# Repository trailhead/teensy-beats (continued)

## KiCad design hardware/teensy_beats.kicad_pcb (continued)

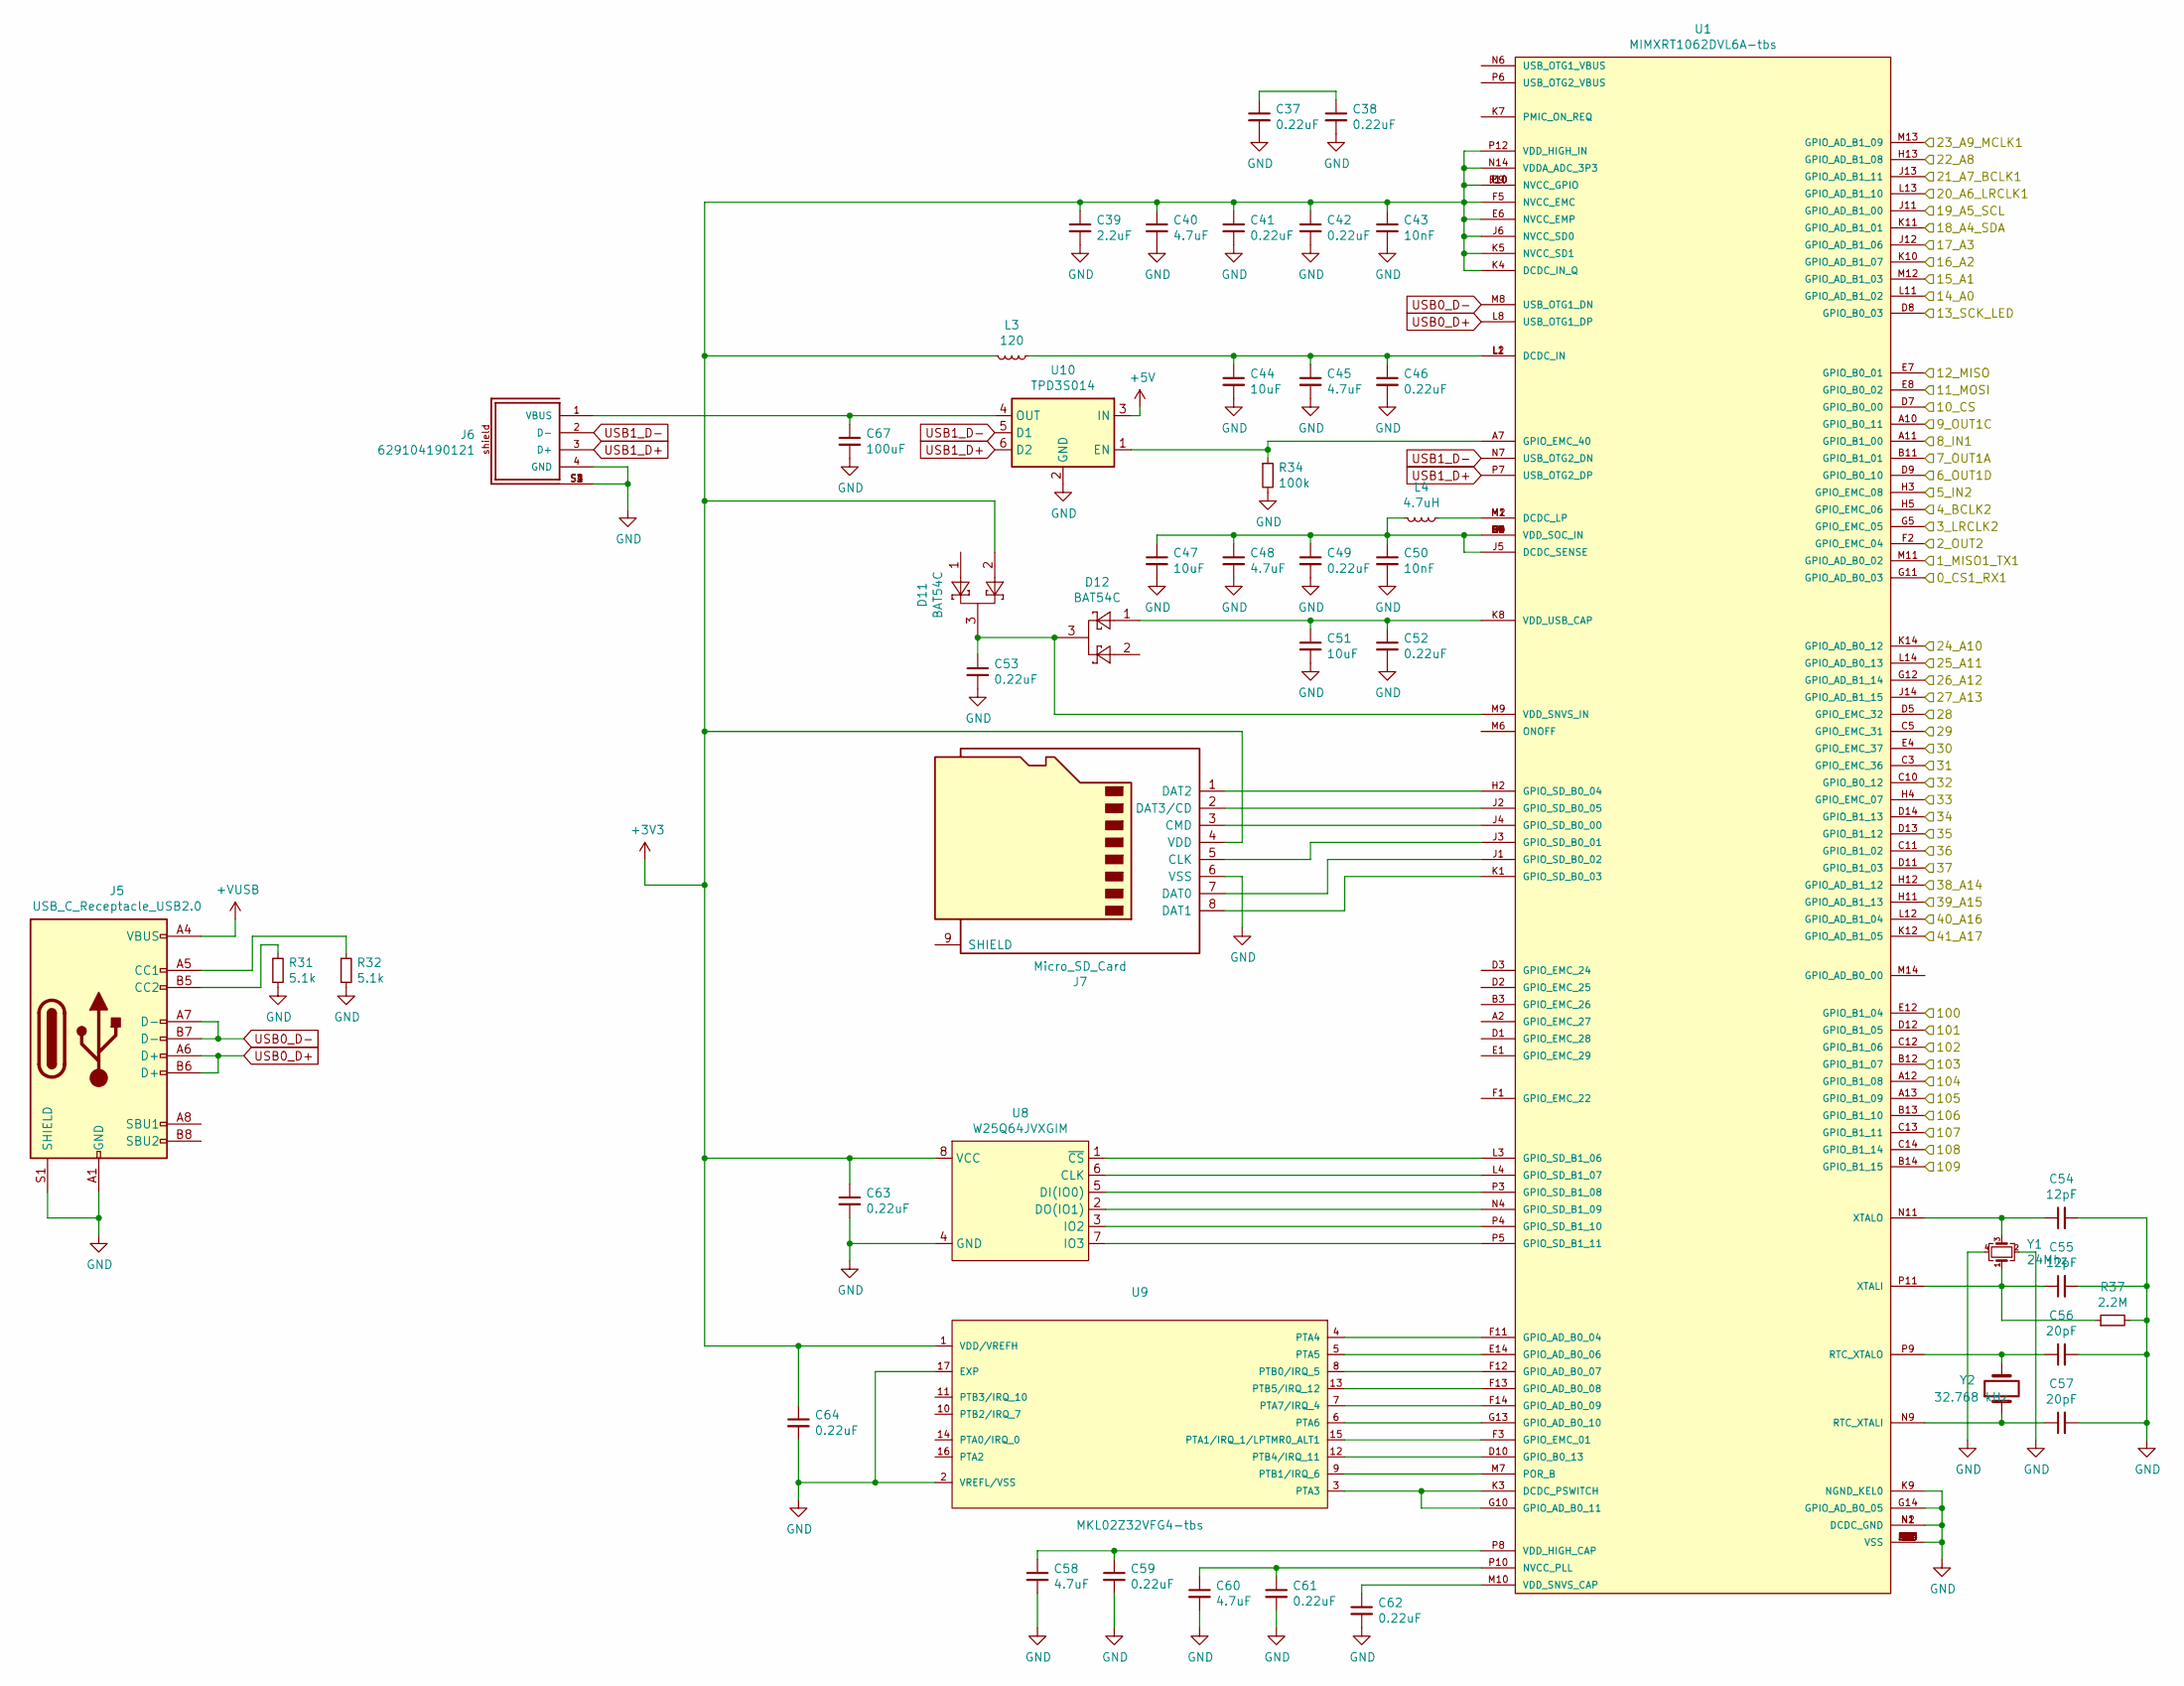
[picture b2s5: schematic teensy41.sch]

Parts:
C37, C38, C41, C42, C46, C49, C52, C53, C59, C61, C62, C63, C64: 0.22uF; C_0402_1005Metric
C39: 2.2uF; C_0805_2012Metric
C40, C45, C48, C58, C60: 4.7uF; C_0603_1608Metric
C43: 10nF; C_0402_1005Metric
C44, C47, C51: 10uF; C_0603_1608Metric
C50: 10nF; C_0603_1608Metric
C54, C55: 12pF; C_0402_1005Metric
C56, C57: 20pF; C_0402_1005Metric
C67: 100uF; C_0603_1608Metric
D11, D12: BAT54C; SOT-23
J5: USB_C_Receptacle_USB2.0; MOLEX_105450-0101
J6: 629104190121; PART-NUMBER 629104190121
J7: Micro_SD_Card; microSD_HC_Wuerth_693072010801
L3: 120; L_0603_1608Metric
L4: 4.7uH; L_1210_3225Metric
R31, R32: 5.1k; R_0402_1005Metric
R34: 100k; R_0402_1005Metric
R37: 2.2M; R_0402_1005Metric
U1: MIMXRT1062DVL6A-tbs; BGA196C80P14X14_1200X1200X161N; PARTREV 1.2
U8: W25Q64JVXGIM; SOIC-8_3.9x4.9mm_P1.27mm
U9: MKL02Z32VFG4-tbs; QFN50P300X300X65-17N
U10: TPD3S014; SOT-23-6
Y1: 24Mhz; Oscillator_SMD_Abracon_ASE-4Pin_3.2x2.5mm
Y2: 32.768 kHz; Crystal_SMD_MicroCrystal_CC7V-T1A-2Pin_3.2x1.5mm

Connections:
+3V3: C39.1, C40.1, C41.1, C42.1, C43.1, C63.1, C64.1, D11.2, J7.4 (VDD), L3.2, U1.E6 (NVCC_EMP), U1.E9 (NVCC_GPIO), U1.F5 (NVCC_EMC), U1.F10 (NVCC_GPIO), U1.J6 (NVCC_SD0), U1.J10 (NVCC_GPIO), U1.K4 (DCDC_IN_Q), U1.K5 (NVCC_SD1), U1.N14 (VDDA_ADC_3P3), U1.P12 (VDD_HIGH_IN), U8.8 (VCC), U9.1 (VDD/VREFH); also elsewhere on the board
+5V: U10.3 (IN); also elsewhere on the board
+VUSB: J5.A4 (VBUS), J5.A9 (VBUS), J5.B4 (VBUS), J5.B9 (VBUS); also elsewhere on the board
/Teensy4.1/15_A1: U1.M12 (GPIO_AD_B1_03)
/Teensy4.1/16_A2: U1.K10 (GPIO_AD_B1_07)
/Teensy4.1/17_A3: U1.J12 (GPIO_AD_B1_06)
/Teensy4.1/26_A12: U1.G12 (GPIO_AD_B1_14)
/Teensy4.1/27_A13: U1.J14 (GPIO_AD_B1_15)
/Teensy4.1/33: U1.H4 (GPIO_EMC_07)
/Teensy4.1/37: U1.D11 (GPIO_B1_03)
/Teensy4.1/40_A16: U1.L12 (GPIO_AD_B1_04)
/Teensy4.1/41_A17: U1.K12 (GPIO_AD_B1_05)
BATT_LEVEL: U1.H12 (GPIO_AD_B1_12); also elsewhere on the board
BATT_STAT1: U1.A10 (GPIO_B0_11); also elsewhere on the board
BATT_STAT2: U1.A11 (GPIO_B1_00); also elsewhere on the board
BCLK: U1.J13 (GPIO_AD_B1_11); also elsewhere on the board
BCLK2: U1.H5 (GPIO_EMC_06); also elsewhere on the board
CS: U1.D7 (GPIO_B0_00); also elsewhere on the board
DOUT2: U1.F2 (GPIO_EMC_04); also elsewhere on the board
E1A: U1.D14 (GPIO_B1_13); also elsewhere on the board
E1B: U1.D13 (GPIO_B1_12); also elsewhere on the board
E2A: U1.C10 (GPIO_B0_12); also elsewhere on the board
E2B: U1.C11 (GPIO_B1_02); also elsewhere on the board
E3A: U1.D5 (GPIO_EMC_32); also elsewhere on the board
E3B: U1.C5 (GPIO_EMC_31); also elsewhere on the board
E4A: U1.E4 (GPIO_EMC_37); also elsewhere on the board
E4B: U1.C3 (GPIO_EMC_36); also elsewhere on the board
GND: C37.2, C38.2, C39.2, C40.2, C41.2, C42.2, C43.2, C44.2, C45.2, C46.2, C47.2, C48.2, C49.2, C50.2, C51.2, C52.2, C53.2, C54.2, C55.2, C56.2, C57.2, C58.2, C59.2, C60.2, C61.2, C62.2, C63.2, C64.2, C67.2, J5.A1 (GND), J5.A12 (GND), J5.B1 (GND), J5.B12 (GND), J5.S1 (SHIELD), J6.4 (GND), J6.S1, J6.S2, J6.S3, J6.S4, J7.6 (VSS), R31.2, R32.2, R34.2, R37.2, U1.A1 (VSS), U1.A14 (VSS), U1.B5 (VSS), U1.B10 (VSS), U1.E2 (VSS), U1.E13 (VSS), U1.G7 (VSS), U1.G8 (VSS), U1.G14 (GPIO_AD_B0_05), U1.H7 (VSS), U1.H8 (VSS), U1.J7 (VSS), U1.J8 (VSS), U1.K2 (VSS), U1.K9 (NGND_KEL0), U1.K13 (VSS), U1.L9 (VSS), U1.N1 (DCDC_GND), U1.N2 (DCDC_GND), U1.N5 (VSS), U1.N8 (VSS), U1.P1 (VSS), U1.P14 (VSS), U8.4 (GND), U9.2 (VREFL/VSS), U9.17 (EXP), U10.2 (GND), Y1.2, Y1.4; also elsewhere on the board
GPANAIO: U1.N10 (GPANAIO)
KEYPAD_C0: U1.B13 (GPIO_B1_10); also elsewhere on the board
KEYPAD_C1: U1.C12 (GPIO_B1_06); also elsewhere on the board
KEYPAD_C2: U1.A13 (GPIO_B1_09); also elsewhere on the board
KEYPAD_C3: U1.B12 (GPIO_B1_07); also elsewhere on the board
KEYPAD_C4: U1.A12 (GPIO_B1_08); also elsewhere on the board
KEYPAD_R0: U1.C13 (GPIO_B1_11); also elsewhere on the board
KEYPAD_R1: U1.C14 (GPIO_B1_14); also elsewhere on the board
KEYPAD_R2: U1.D12 (GPIO_B1_05); also elsewhere on the board
KEYPAD_R3: U1.E12 (GPIO_B1_04); also elsewhere on the board
KEYPAD_R4: U1.B14 (GPIO_B1_15); also elsewhere on the board
LRCLK: U1.L13 (GPIO_AD_B1_10); also elsewhere on the board
LRCLK2: U1.G5 (GPIO_EMC_05); also elsewhere on the board
MCLK: U1.M13 (GPIO_AD_B1_09); also elsewhere on the board
MISO: U1.E7 (GPIO_B0_01); also elsewhere on the board
MOSI: U1.E8 (GPIO_B0_02); also elsewhere on the board
unnamed: C37.1, C38.1
unnamed: C44.1, C45.1, C46.1, L3.1, U1.L1 (DCDC_IN), U1.L2 (DCDC_IN)
unnamed: C47.1, C48.1, C49.1, C50.1, L4.2, U1.F6 (VDD_SOC_IN), U1.F7 (VDD_SOC_IN), U1.F8 (VDD_SOC_IN), U1.F9 (VDD_SOC_IN), U1.G6 (VDD_SOC_IN), U1.G9 (VDD_SOC_IN), U1.H6 (VDD_SOC_IN), U1.H9 (VDD_SOC_IN), U1.J5 (DCDC_SENSE), U1.J9 (VDD_SOC_IN)
unnamed: C51.1, C52.1, D12.1, U1.K8 (VDD_USB_CAP)
unnamed: C53.1, D11.3, D12.3, U1.M9 (VDD_SNVS_IN)
unnamed: C54.1, U1.N11 (XTALO), Y1.3
unnamed: C55.1, R37.1, U1.P11 (XTALI), Y1.1
unnamed: C56.1, U1.P9 (RTC_XTALO), Y2.2
unnamed: C57.1, U1.N9 (RTC_XTALI), Y2.1
unnamed: C58.1, C59.1, U1.P8 (VDD_HIGH_CAP)
unnamed: C60.1, C61.1, U1.P10 (NVCC_PLL)
unnamed: C62.1, U1.M10 (VDD_SNVS_CAP)
unnamed: C67.1, J6.1 (VBUS), U10.4 (OUT)
unnamed: J5.A5 (CC1), R32.1
unnamed: J5.B5 (CC2), R31.1
unnamed: J7.1 (DAT2), U1.H2 (GPIO_SD_B0_04)
unnamed: J7.2 (DAT3/CD), U1.J2 (GPIO_SD_B0_05)
unnamed: J7.3 (CMD), U1.J4 (GPIO_SD_B0_00)
unnamed: J7.5 (CLK), U1.J3 (GPIO_SD_B0_01)
unnamed: J7.7 (DAT0), U1.J1 (GPIO_SD_B0_02)
unnamed: J7.8 (DAT1), U1.K1 (GPIO_SD_B0_03)
unnamed: L4.1, U1.M1 (DCDC_LP), U1.M2 (DCDC_LP)
unnamed: R34.1, U1.A7 (GPIO_EMC_40), U10.1 (EN)
unnamed: U1.D10 (GPIO_B0_13), U9.12 (PTB4/IRQ_11)
unnamed: U1.E14 (GPIO_AD_B0_06), U9.5 (PTA5)
unnamed: U1.F3 (GPIO_EMC_01), U9.15 (PTA1/IRQ_1/LPTMR0_ALT1)
unnamed: U1.F11 (GPIO_AD_B0_04), U9.4 (PTA4)
unnamed: U1.F12 (GPIO_AD_B0_07), U9.8 (PTB0/IRQ_5)
unnamed: U1.F13 (GPIO_AD_B0_08), U9.13 (PTB5/IRQ_12)
unnamed: U1.F14 (GPIO_AD_B0_09), U9.7 (PTA7/IRQ_4)
unnamed: U1.G10 (GPIO_AD_B0_11), U1.K3 (DCDC_PSWITCH), U9.3 (PTA3)
unnamed: U1.G13 (GPIO_AD_B0_10), U9.6 (PTA6)
unnamed: U1.L3 (GPIO_SD_B1_06), U8.1 (~CS)
unnamed: U1.L4 (GPIO_SD_B1_07), U8.6 (CLK)
unnamed: U1.M7 (POR_B), U9.9 (PTB1/IRQ_6)
unnamed: U1.N4 (GPIO_SD_B1_09), U8.2 (DO(IO1))
unnamed: U1.P3 (GPIO_SD_B1_08), U8.5 (DI(IO0))
unnamed: U1.P4 (GPIO_SD_B1_10), U8.3 (IO2)
unnamed: U1.P5 (GPIO_SD_B1_11), U8.7 (IO3)
PCTL: U1.B11 (GPIO_B1_01); also elsewhere on the board
PHONE_DET: U1.H11 (GPIO_AD_B1_13); also elsewhere on the board
PWR_BTN: U1.K14 (GPIO_AD_B0_12); also elsewhere on the board
REC_LED: U1.H3 (GPIO_EMC_08); also elsewhere on the board
RGB_CLOCK: U1.M11 (GPIO_AD_B0_02); also elsewhere on the board
RGB_DATA: U1.G11 (GPIO_AD_B0_03); also elsewhere on the board
SCL: U1.J11 (GPIO_AD_B1_00); also elsewhere on the board
SCLK: U1.D8 (GPIO_B0_03); also elsewhere on the board
SDA: U1.K11 (GPIO_AD_B1_01); also elsewhere on the board
TFT_CS: U1.D9 (GPIO_B0_10); also elsewhere on the board
TFT_DC: U1.H13 (GPIO_AD_B1_08); also elsewhere on the board
TOUCH_CS: U1.L11 (GPIO_AD_B1_02); also elsewhere on the board
USB0_D+: J5.A6 (D+), J5.B6 (D+), U1.L8 (USB_OTG1_DP)
USB0_D-: J5.A7 (D-), J5.B7 (D-), U1.M8 (USB_OTG1_DN)
USB1_D+: J6.3 (D+), U1.P7 (USB_OTG2_DP), U10.6 (D2)
USB1_D-: J6.2 (D-), U1.N7 (USB_OTG2_DN), U10.5 (D1)
VOLUME: U1.L14 (GPIO_AD_B0_13); also elsewhere on the board

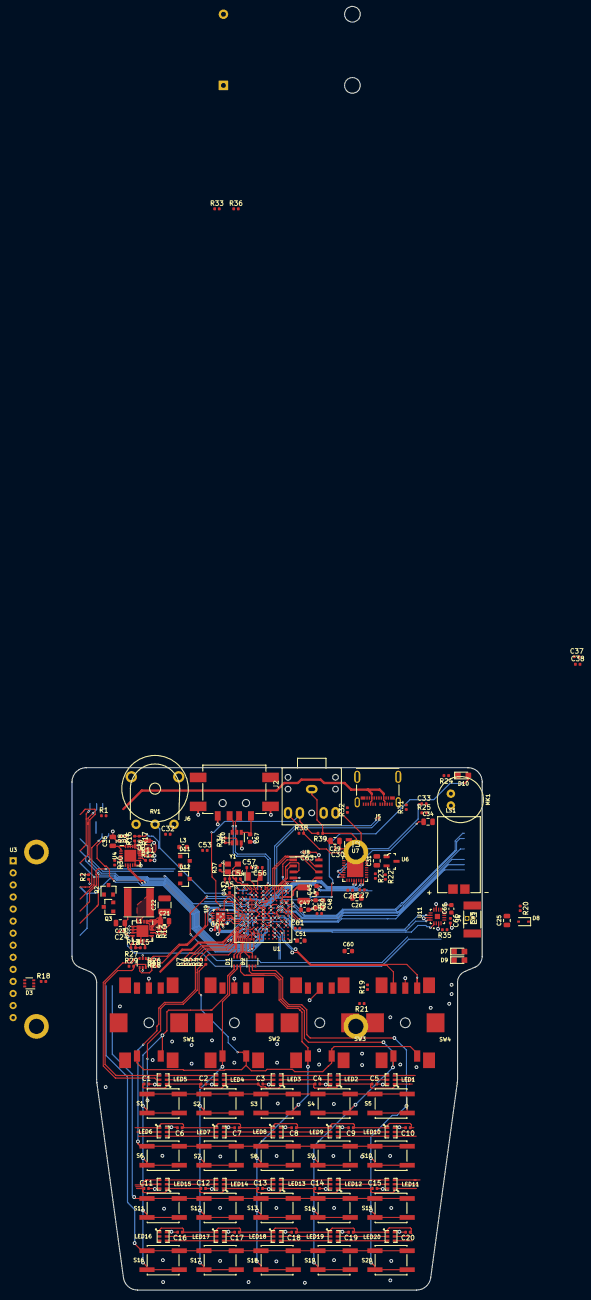
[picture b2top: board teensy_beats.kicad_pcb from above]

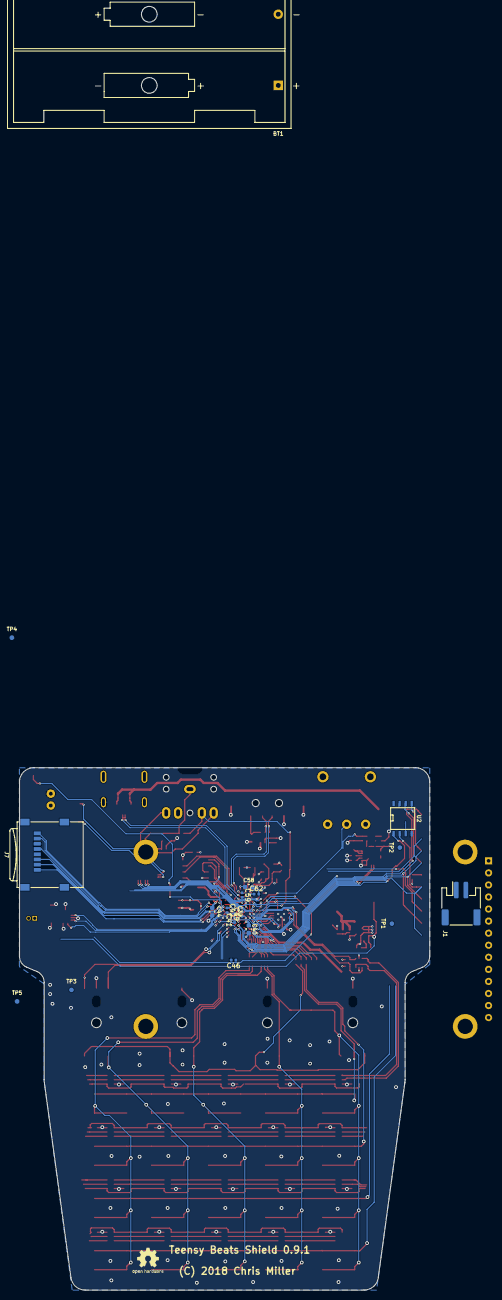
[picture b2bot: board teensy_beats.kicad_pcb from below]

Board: 4 copper layers, 86.4 x 110.0 mm, 195 parts (19 on the bottom side), 171 nets.

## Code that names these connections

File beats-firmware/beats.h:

#ifndef __BEATS_H__
#define __BEATS_H__

#include <stdint.h>
#include <Audio.h>
#include "ILI9341_t3.h"
#include "font_Arial.h"
#include "cb_encoder.h"
#include "instrument.h"

#define NUM_BUTTON_ROWS       5
#define NUM_BUTTON_COLS       5
#define KEYPAD_ROW_0          28
#define KEYPAD_ROW_1          29
#define KEYPAD_ROW_2          30
#define KEYPAD_ROW_3          31
#define KEYPAD_ROW_4          27
#define KEYPAD_COL_0          35
#define KEYPAD_COL_1          36
#define KEYPAD_COL_2          37
#define KEYPAD_COL_3          38
#define KEYPAD_COL_4          39

#define NUMROWS               4
#define NUMCOLS               4
#define NUMCOLS               4
#define NUMINST               4
#define NUMTICKS              (NUMROWS*NUMCOLS)
#define BUTTON_DEBOUNCE       250
#define VBAT_PIN              A10
#define VBAT_DIVIDER          2.0f

#define SCREEN_HEIGHT         240
#define SCREEN_WIDTH          320

#define PCTL_PIN              5
#define PWR_BTN_PIN           A11
#define SHUTDOWN_HOLD_TIME    3000

#define BATT_STAT1_PIN        15
#define BATT_STAT2_PIN        16
#define HIZ_TIMEOUT           500 // ms of stable state to reset high-z state
#define HIZ_COUNT             3   // minimum pin changes under HIZ_TIMEOUT to indicate we're in high-z state

#define SDCARD_CS_PIN         BUILTIN_SDCARD

// Time interval for serial status in ms
#define STATUS_INTERVAL       2000

#define NUMPIXELS 20 // Number of LEDs in strip

// RGB LED pins
#define DATAPIN               1
#define CLOCKPIN              0

#define NUM_LED_COLS          5
#define NUM_LED_ROWS          4

// For optimized ILI9341_t3 library
#define TFT_DC                10
#define TFT_CS                21
#define TFT_RST               255  // 255 = unused, connect to 3.3V
#define TFT_MOSI              7
#define TFT_SCLK              14
#define TFT_MISO              12

#define TOUCH_CS              33
#define TFT_INTERVAL          50

extern ILI9341_t3 tft;

extern int tick;
extern int current_inst;
extern uint8_t notes[NUMINST][NUMROWS][NUMCOLS];
extern boolean playing;
extern boolean sd_inserted;
extern float bpm;
extern float tones[12];

extern WaveformInstrument wf_inst1;
extern WaveformInstrument wf_inst2;
extern WaveformInstrument wf_inst3;

extern CallbackEncoder encoder1;
extern CallbackEncoder encoder2;
extern CallbackEncoder encoder3;
extern CallbackEncoder encoder4;

#define DEFAULT_NOTE          1

typedef struct {
  uint8_t note;
  uint8_t octave;
  uint8_t vol;
  int8_t pan; 
} noteinfo;

float mix_l_gain_from_pan(float pan);
float mix_r_gain_from_pan(float pan);
void play_note(uint16_t which_note);
float tone_to_freq(uint16_t note, uint16_t octave);
void clear_channel(uint8_t channel);

#endif // __BEATS_H___

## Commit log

2018-09-16 aaddign files
2018-09-17 trying pins 0 and 1 for apa102
2018-09-17 ordered 0.9.0
2018-09-17 mass rename
2018-09-17 updating bom
2018-09-17 rearranged dirs
2018-09-19 abstracting UI
2018-09-21 further abstracting instruments and UI
2018-09-21 adding keyboard ui
2018-09-22 screen navigation working, callbacks on buttons, fixed battery charging indicator
2018-09-22 adding effect bypass testing
2018-09-27 real hardware!
2018-09-28 reworking audio setup for banks
2018-09-29 polyphonic sound banks and UI improvements
2018-09-29 fixing incorrect PWR_BUTTON net on schematic and PCB
2018-09-29 moving firmware files
2018-10-17 code changes for hackaday prize round 5 entry.
2018-10-17 changed pin mapping to add pg signal, added enable jumper for development. adding updated gerbers.
2018-10-22 moving bom into github pages directory
2018-10-22 mcfly? github not updating
2018-10-22 github not updating.
2018-10-30 adding board outline svg files
2018-10-30 fixed battery voltage pin for 0.9.0 PCB
2019-01-05 pin changes in firmware for 0.9.1
2020-11-30 start of k66 based v2 design
2021-02-08 v2 mostly routed
